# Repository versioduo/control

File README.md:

# control

⚙️ Instrument Controller

## Board

## Schematic

[PDF](control.pdf)

## Bill Of Materials

[Interactive BOM](https://htmlpreview.github.io/?https://github.com/versioduo/control/main/control-bom.html)

# Copying
Anyone can use this public domain work without having to seek authorisation, no one can ever own it.

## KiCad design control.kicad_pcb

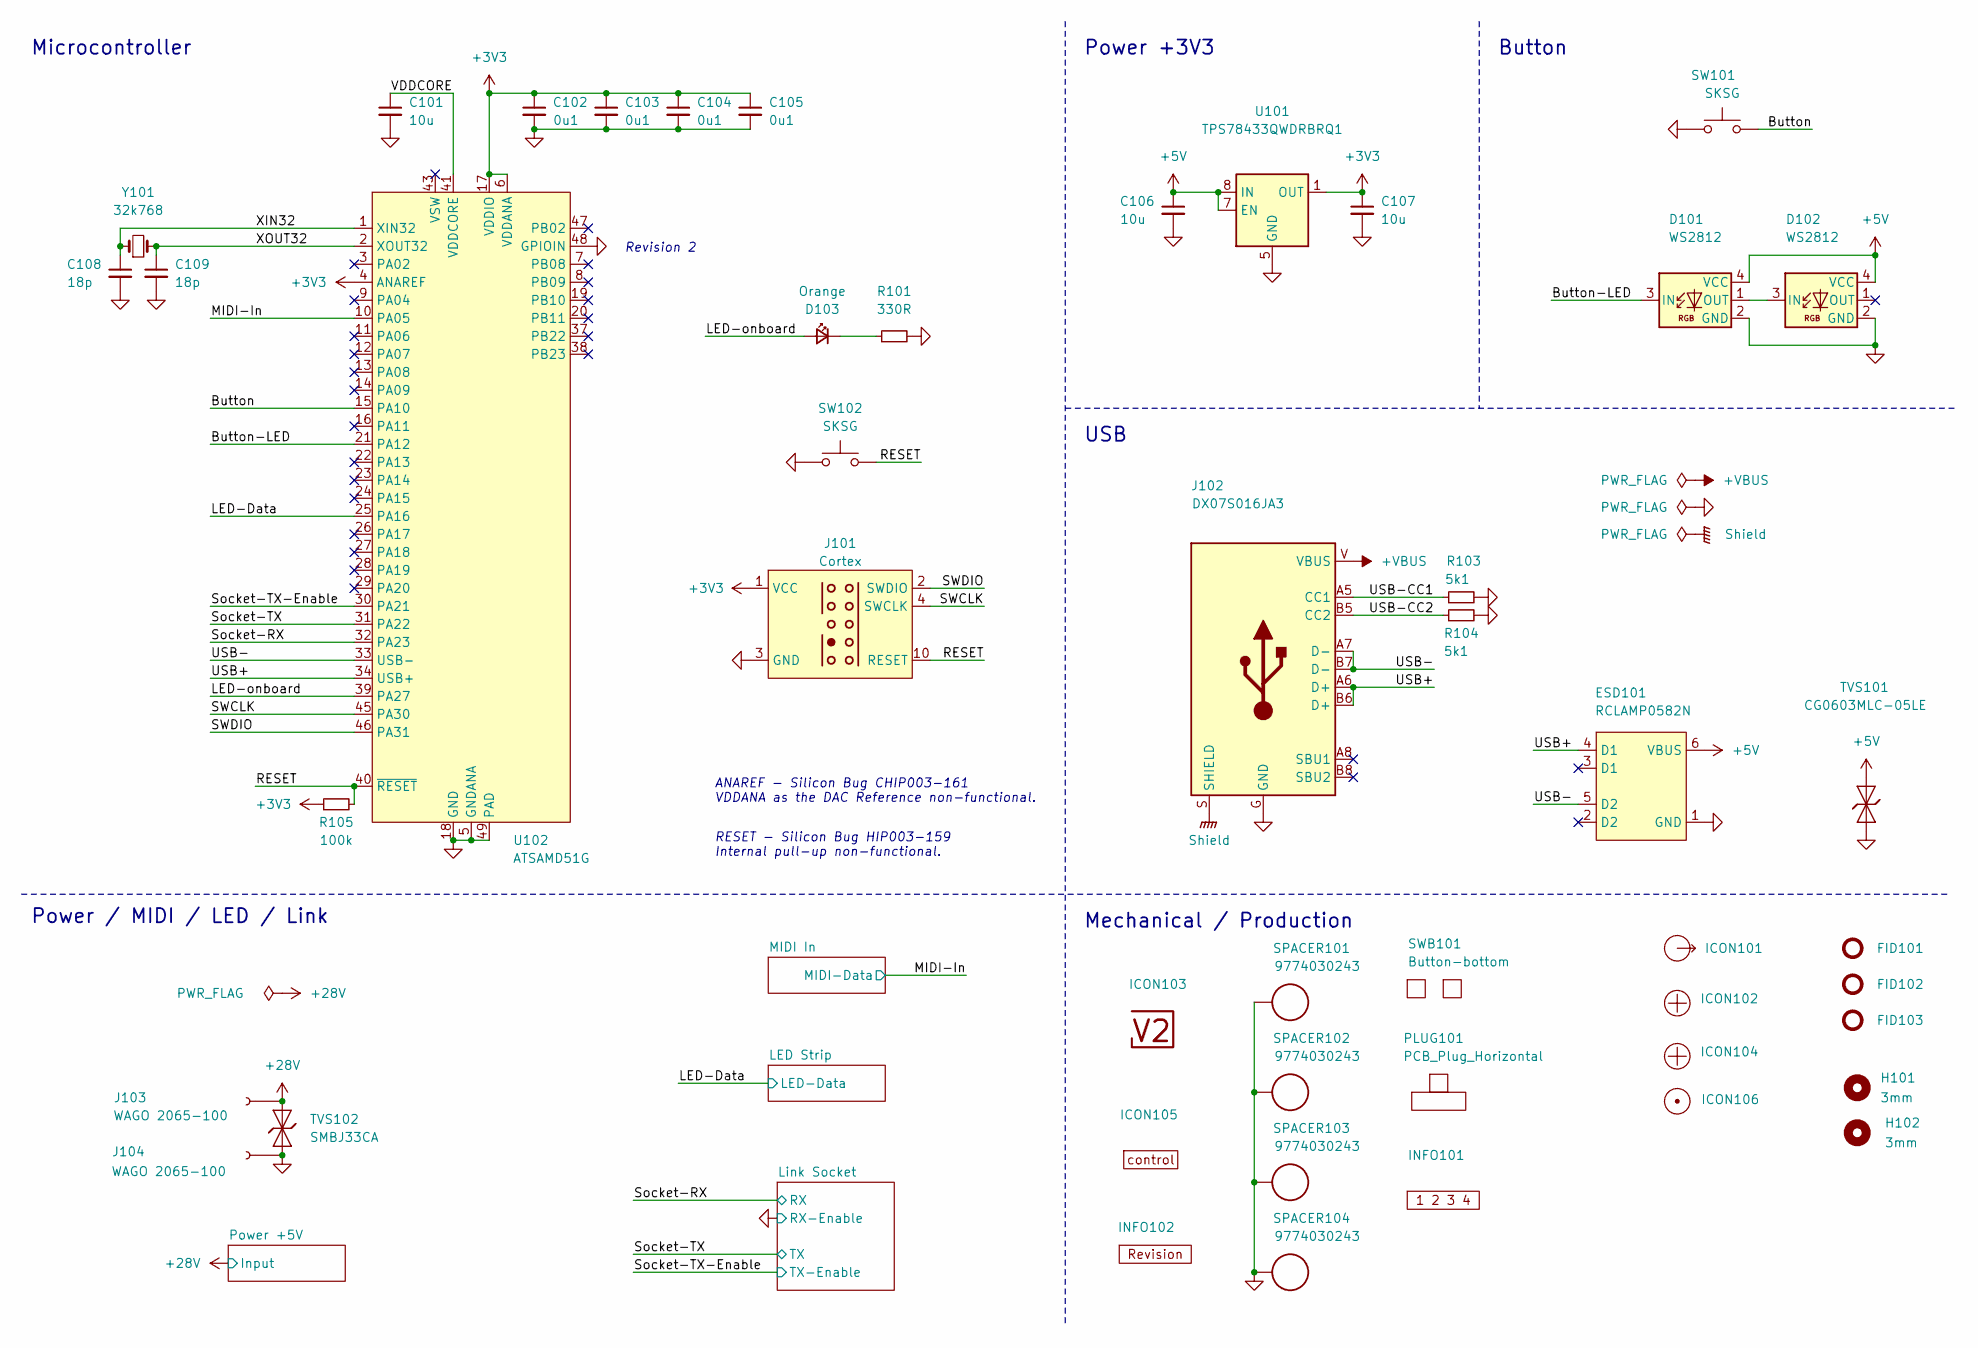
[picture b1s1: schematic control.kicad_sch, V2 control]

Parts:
C101: 10u; C_0603; Rating 10V; Mouser 810-C1608X6S1A106M
C102, C103, C104, C105: 0u1; C_0603; Rating 50V; Mouser 810-CGA3E2X7R1H104MA
C106, C107: 10u; C_0805; Rating 25V; Mouser 810-C2012X5R1E106K
C108, C109: 18p; C_0603; Rating 50V; Mouser 810-CGA3E2C0G1H180J
D101, D102: WS2812; WS2812-2020; LCSC C965555
D103: Orange; LED_0603; Mouser 755-SML-D12D1WT86
ESD101: RCLAMP0582N; SLP1210N6; Mouser 947-RCLAMP0582N.TCT
FID101, FID102, FID103: Fiducial_Paste; Fiducial_0.5mm_Mask1mm_Paste
H101, H102: 3mm; MountingHole_3mm
ICON101: Arrow_Out
ICON102, ICON104: Plus; Plus_Small
ICON103: V2-logo; Logo_Small
ICON105: Board_control; Board_control_Small
ICON106: Dot; Dot_Small
INFO101: Layer_Numbers
INFO102: Revision
J101: Cortex
J102: DX07S016JA3; JAE_DX07S016JA3; Mouser 656-DX07S016JA3R1500
J103, J104: WAGO 2065-100; 2065-100
PLUG101: PCB_Plug_Horizontal
R101: 330R; R_0603; Rating 100mW; Mouser 71-CRCW0603330RFKEAC
R103, R104: 5k1; R_0603; Rating 100mW; Mouser 71-CRCW06035K10FKEAC
R105: 100k; R_0603; Rating 100mW; Mouser 71-CRCW0603100KFKEAC
SPACER101, SPACER102, SPACER103, SPACER104: 9774030243
SW101, SW102: SKSG; Rating 1.6N; Mouser 688-SKSGACE010
SWB101: Button-bottom; PCB_Button-bottom
TVS101: CG0603MLC-05LE; D_0603; Rating 5V; Mouser 652-CG0603MLC-05LE
TVS102: SMBJ33CA; D_SMB; Rating 33V; Mouser 652-SMBJ33CA-Q
U101: TPS78433QWDRBRQ1; VSON-8-1_3x3mm_P0.65_EP1.65x2.4mm; Mouser 595-TPS78433QWDRBRQ1
U102: ATSAMD51G; QFN-48-1EP_7x7mm_P0.5mm_EP5.45x5.45mm_ThermalVias; Mouser 556-ATSAMD51G19AMU
Y101: 32k768; Crystal_SMD_3215-2Pin_3.2x1.5mm; Mouser 815-ABS0716632.768KT

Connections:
+3V3: C102.1, C103.1, C104.1, C105.1, C107.1, J101.1 (VCC), R105.1, U101.1 (OUT), U102.4 (ANAREF), U102.6 (VDDANA), U102.17 (VDDIO), U102.36 (VDDIO), U102.44 (VDDIO); also elsewhere on the board
+5V: C106.1, D101.4 (VCC), D102.4 (VCC), ESD101.6 (VBUS), TVS101.2 (A), U101.7 (EN), U101.8 (IN); also elsewhere on the board
+28V: J103.1, TVS102.2 (A); also elsewhere on the board
/+VBUS: J102.V (VBUS)
/Button: SW101.2, U102.15 (PA10)
/Button-LED: D101.3 (IN), U102.21 (PA12)
/LED-Data: U102.25 (PA16); also elsewhere on the board
/LED-onboard: D103.2 (A), U102.39 (PA27)
/MIDI-In: U102.10 (PA05); also elsewhere on the board
/RESET: J101.10 (RESET), R105.2, SW102.2, U102.40 (~RESET)
/SWCLK: J101.4 (SWCLK), U102.45 (PA30)
/SWDIO: J101.2 (SWDIO), U102.46 (PA31)
/Shield: J102.S (SHIELD)
/Socket-RX: U102.32 (PA23); also elsewhere on the board
/Socket-TX: U102.31 (PA22); also elsewhere on the board
/Socket-TX-Enable: U102.30 (PA21); also elsewhere on the board
/USB+: ESD101.4 (D1), J102.A6 (D+), J102.B6 (D+), U102.34 (USB+)
/USB-: ESD101.5 (D2), J102.A7 (D-), J102.B7 (D-), U102.33 (USB-)
/USB-CC1: J102.A5 (CC1), R103.1
/USB-CC2: J102.B5 (CC2), R104.1
/VDDCORE: C101.1, U102.41 (VDDCORE)
/XIN32: C108.1, U102.1 (XIN32), Y101.1
/XOUT32: C109.1, U102.2 (XOUT32), Y101.2
GND: C101.2, C102.2, C103.2, C104.2, C105.2, C106.2, C107.2, C108.2, C109.2, D101.2 (GND), D102.2 (GND), ESD101.1 (GND), J101.3 (GND), J101.5 (GND), J102.G (GND), J104.1, R101.2, R103.2, R104.2, SPACER101.1 (1_1), SPACER102.1 (1_1), SPACER103.1 (1_1), SPACER104.1 (1_1), SW101.1, SW102.1, TVS101.1 (K), TVS102.1 (K), U101.5 (GND), U101.9 (GND), U102.5 (GNDANA), U102.18 (GND), U102.35 (GND), U102.42 (GND), U102.48 (GPIOIN), U102.49 (PAD); also elsewhere on the board
unnamed: D101.1 (OUT), D102.3 (IN)
unnamed: D103.1 (K), R101.1

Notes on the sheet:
ANAREF - ﻿Silicon Bug CHIP003-161 VDDANA as the DAC Reference non-functional.
Power / MIDI / LED / Link
RESET - ﻿Silicon Bug HIP003-159 Internal pull-up non-functional.
Button
Revision 2
Power +3V3
Mechanical / Production
Microcontroller
USB

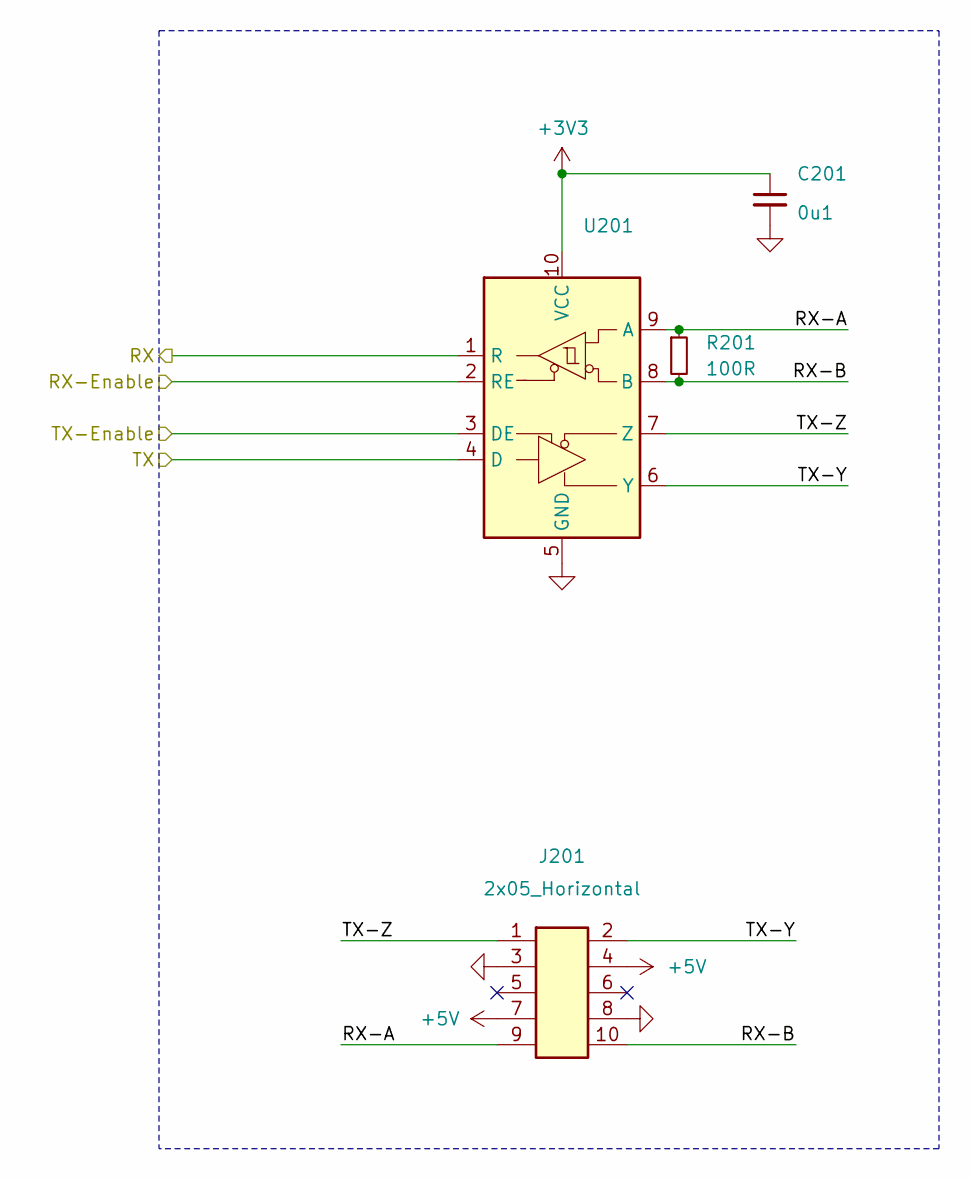
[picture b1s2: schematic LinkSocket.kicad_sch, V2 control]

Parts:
C201: 0u1; C_0603; Rating 50V; Mouser 810-CGA3E2X7R1H104MA
J201: 2x05_Horizontal; PinHeader_2x05_P1.27mm_Horizontal; Mouser 649-200211120001T4LF
R201: 100R; R_0603; Rating 330mW; Mouser 71-CRCW0603100RFKEAH
U201: VSON-10-4-1EP_3x3mm_P0.5mm_EP1.65x2.4mm_ThermalVias

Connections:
+3V3: C201.1, U201.10 (VCC); also elsewhere on the board
+5V: J201.4, J201.7; also elsewhere on the board
/Link Socket/RX-A: J201.9, R201.1, U201.9 (A)
/Link Socket/RX-B: J201.10, R201.2, U201.8 (B)
/Link Socket/TX-Y: J201.2, U201.6 (Y)
/Link Socket/TX-Z: J201.1, U201.7 (Z)
/Socket-RX: U201.1 (R); also elsewhere on the board
/Socket-TX: U201.4 (D); also elsewhere on the board
/Socket-TX-Enable: U201.3 (DE); also elsewhere on the board
GND: C201.2, J201.3, J201.8, U201.2 (RE), U201.5 (GND), U201.11 (GND); also elsewhere on the board

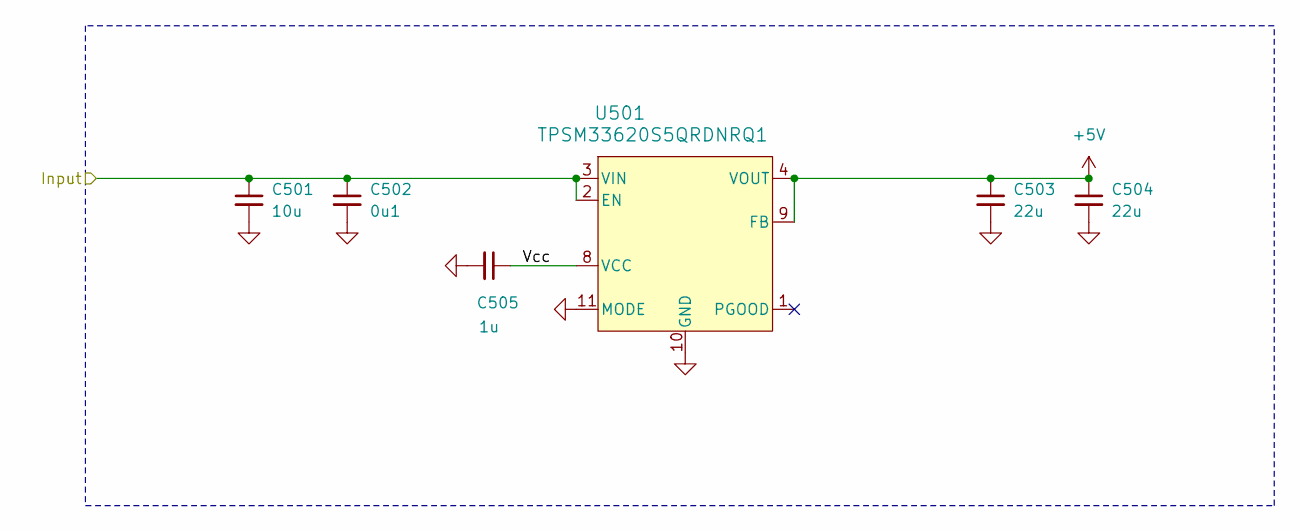
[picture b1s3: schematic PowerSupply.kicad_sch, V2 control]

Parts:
C501: 10u; C_1210; Rating 50V; Mouser 810-CNC6P1X7R1H106K2
C502: 0u1; C_0603; Rating 50V; Mouser 810-CGA3E2X7R1H104MA
C503, C504: 22u; C_1210; Rating 25V; Mouser 810-CGA6P3X7R1E226M5
C505: 1u; C_0603; Rating 50V; Mouser 810-CGA3E3X7R1H105K0
U501: TPSM33620S5QRDNRQ1; QFN-11; Rating 2A; Mouser 595-SM33620S5QRDNRQ1

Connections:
+5V: C503.1, C504.1, U501.4 (VOUT), U501.9 (FB); also elsewhere on the board
+28V: C501.1, C502.1, U501.2 (EN), U501.3 (VIN); also elsewhere on the board
/Power +5V/Vcc: C505.1, U501.8 (VCC)
GND: C501.2, C502.2, C503.2, C504.2, C505.2, U501.10 (GND), U501.11 (MODE); also elsewhere on the board

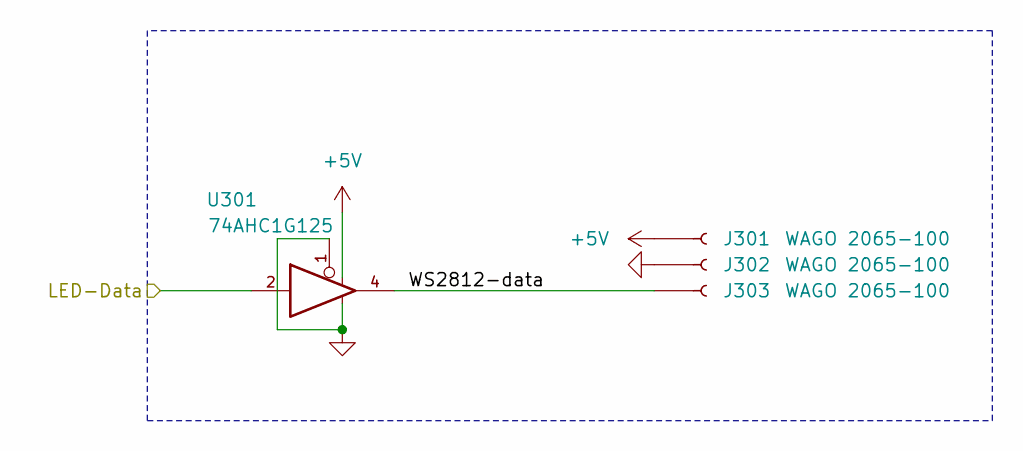
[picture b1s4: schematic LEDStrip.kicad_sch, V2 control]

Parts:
J301, J302, J303: WAGO 2065-100; 2065-100
U301: 74AHC1G125; SOT-23-5; Mouser 595-SN74AHC1G125DBVR

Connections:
+5V: J301.1, U301.5; also elsewhere on the board
/LED Strip/WS2812-data: J303.1, U301.4
/LED-Data: U301.2; also elsewhere on the board
GND: J302.1, U301.1, U301.3; also elsewhere on the board

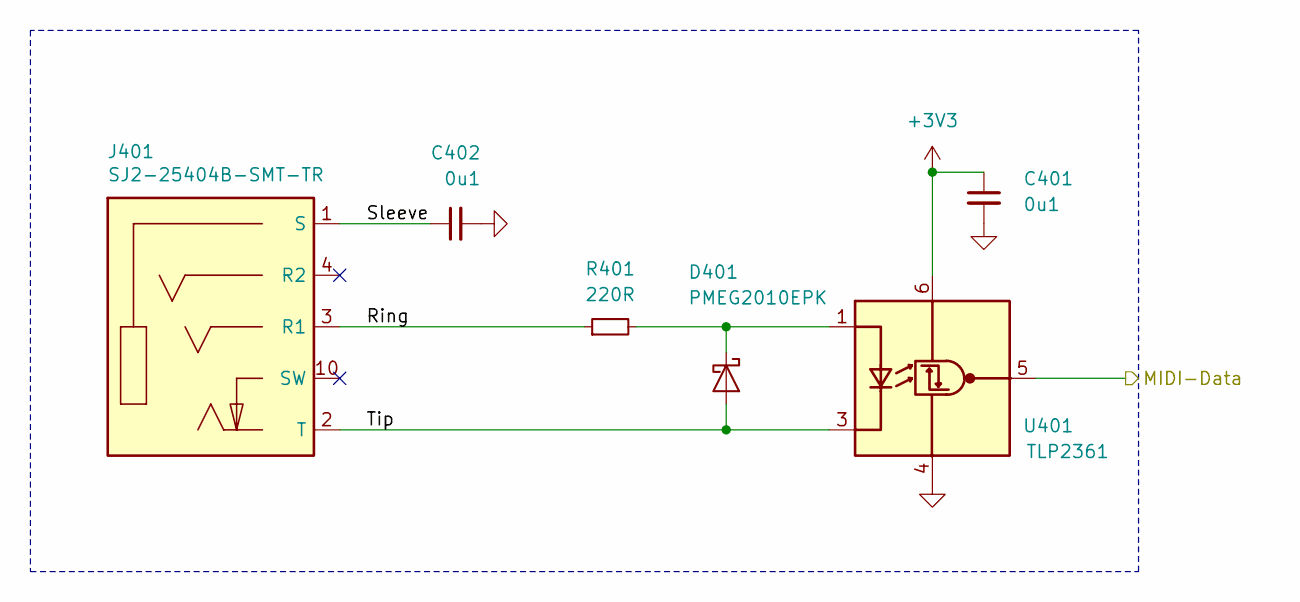
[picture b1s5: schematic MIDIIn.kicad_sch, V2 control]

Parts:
C401, C402: 0u1; C_0603; Rating 50V; Mouser 810-CGA3E2X7R1H104MA
D401: PMEG2010EPK; D_SOD-1608; Rating 20V; Mouser 771-PMEG2010EPK
J401: SJ2-25404B-SMT-TR; CUI_SJ2-25404B-SMT-TR; Mouser 490-SJ2-25404BSMT-TR
R401: 220R; R_0603; Rating 330mW; Mouser 71-CRCW0603220RFKEAH
U401: TLP2361; SO-5-6_4.55x3.7mm_P1.27mm; Mouser 757-TLP2361TPRE

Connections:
+3V3: C401.1, U401.6 (VDD); also elsewhere on the board
/MIDI In/Ring: J401.3 (R1), R401.1
/MIDI In/Sleeve: C402.1, J401.1 (S)
/MIDI In/Tip: D401.2 (A), J401.2 (T), U401.3 (K)
/MIDI-In: U401.5 (VO); also elsewhere on the board
GND: C401.2, C402.2, U401.4 (GND); also elsewhere on the board
unnamed: D401.1 (K), R401.2, U401.1 (A)

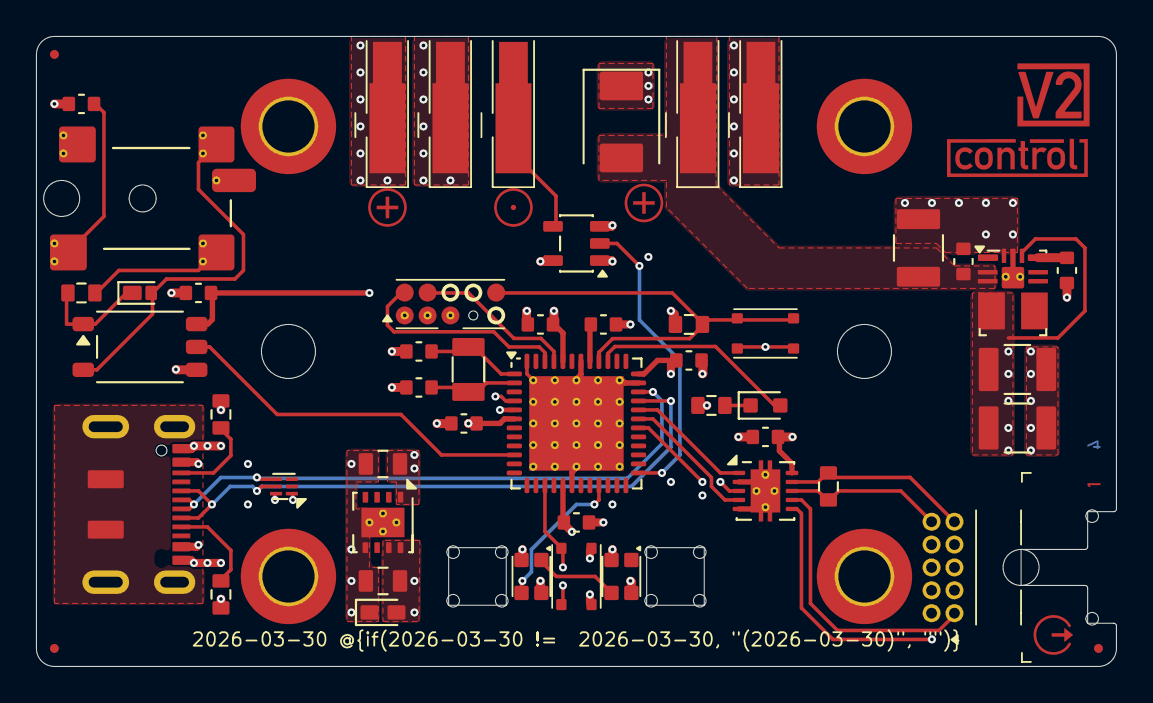
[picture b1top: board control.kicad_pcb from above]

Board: 4 copper layers, 60.0 x 35.0 mm, 67 parts (0 on the bottom side), 34 nets.

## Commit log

2025-11-28 Link termination
2025-12-26 Update project name and BOM link in README
2026-02-13 Replace Order_Number
2026-02-15 Update Library
2026-02-24 Refresh
2026-03-14 Update ESD suppressor
2026-03-30 Replace diode
2026-03-31 Replace step-down
2026-05-11 Good Bye Imperial
